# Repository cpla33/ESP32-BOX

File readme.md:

# ESP32-BOX

The device has been designed around regular ESP32-module to be fitted inside DIN-rail mounting enclosure. The board designed to be compact as much as possible. It takes 3 DIN-rail positions only.

------

### Main features:

- The **ESP32-BOX** has internal AC/DC-converter. Thus it could be powered from the regular AC line (i.e. wall socket) 100-240V (no external AC/DC adapters needed);
- The **ESP32-BOX** provides 4 optically isolated Relay outputs (up to 10A/250V or 5A/30V each). Each relay output has its own LED-indicator.
- The **ESP32-BOX** provides 4 GPIOs. Two of them could be used as I2C-line.
- All the inputs and outputs of the **ESP32-BOX** are implemented as reliable screw terminals.
- The **ESP32-BOX** has onboard RGB-led, which could be used for multiple status indications on your taste.
- The top part of the enclosure is transparent. So the LEDs could be easily observed from the outside.
- The **ESP32-BOX** provides powerful external antenna, which is located inside the enclosure. Thanks to `uFL/IPEX1` header any other suitable antenna could be used instead.
- The **ESP32-BOX** is equipped with the external +3dBi antenna hidden inside the enclosure;
- The **ESP32-BOX** could be programmed with the USB Type-C cable (no buttons required).
- The **ESP32-BOX** could be programmed with the ; write your sketches whenever you want: Arduino, CircuitPython, MicroPython or ESP-IDF.
- Finally, **ESP32-BOX** is **ESPHome**-compatible!

------

### Programming:

A number of different IDEs and programming languages of any taste as below are allowed to program the **ESP32-BOX**:

[ESPHome](https://www.binarytechlabs.com/how-to-flash-esphome-firmware-a-friendly-step-by-step-guide/)

[Arduino](https://randomnerdtutorials.com/installing-the-esp32-board-in-arduino-ide-windows-instructions/)

[CircuitPython](FIRMWARE/CIRCUITPYTHON/readme_circuitpython.md)

[MicroPython](https://micropython.org/download/ESP32_GENERIC/)

[ESP-IDF](https://docs.espressif.com/projects/esp-idf/en/stable/esp32/get-started/index.html)

A couple of different examples could be found in the [FIRMWARE](FIRMWARE/) folder.

------

### Pinout:

------

### Schematics:

Refer to the [schematics](HARDWARE/esp32_box_single.pdf) if needed.

------

Coming soon at Lectronz.com

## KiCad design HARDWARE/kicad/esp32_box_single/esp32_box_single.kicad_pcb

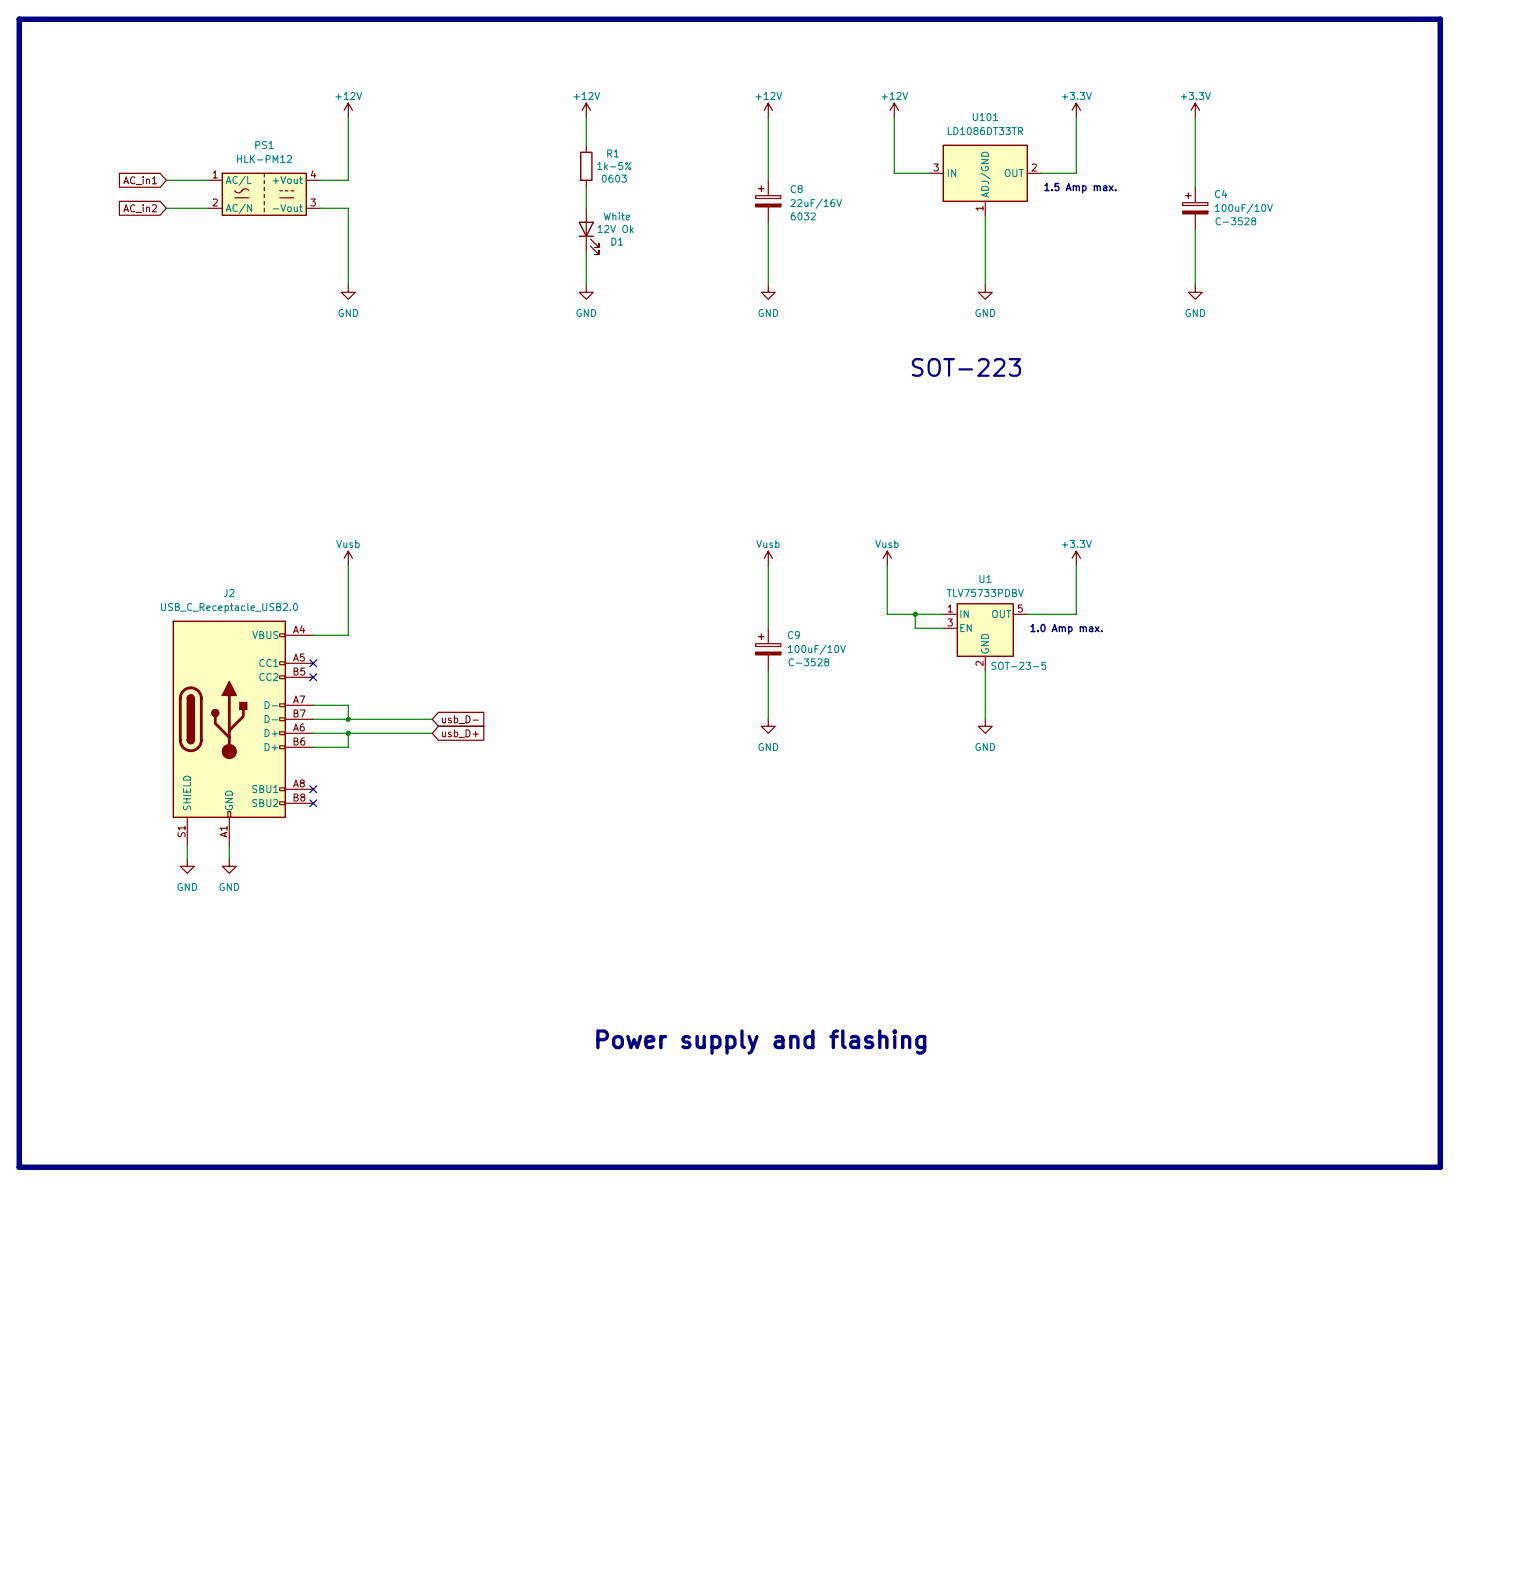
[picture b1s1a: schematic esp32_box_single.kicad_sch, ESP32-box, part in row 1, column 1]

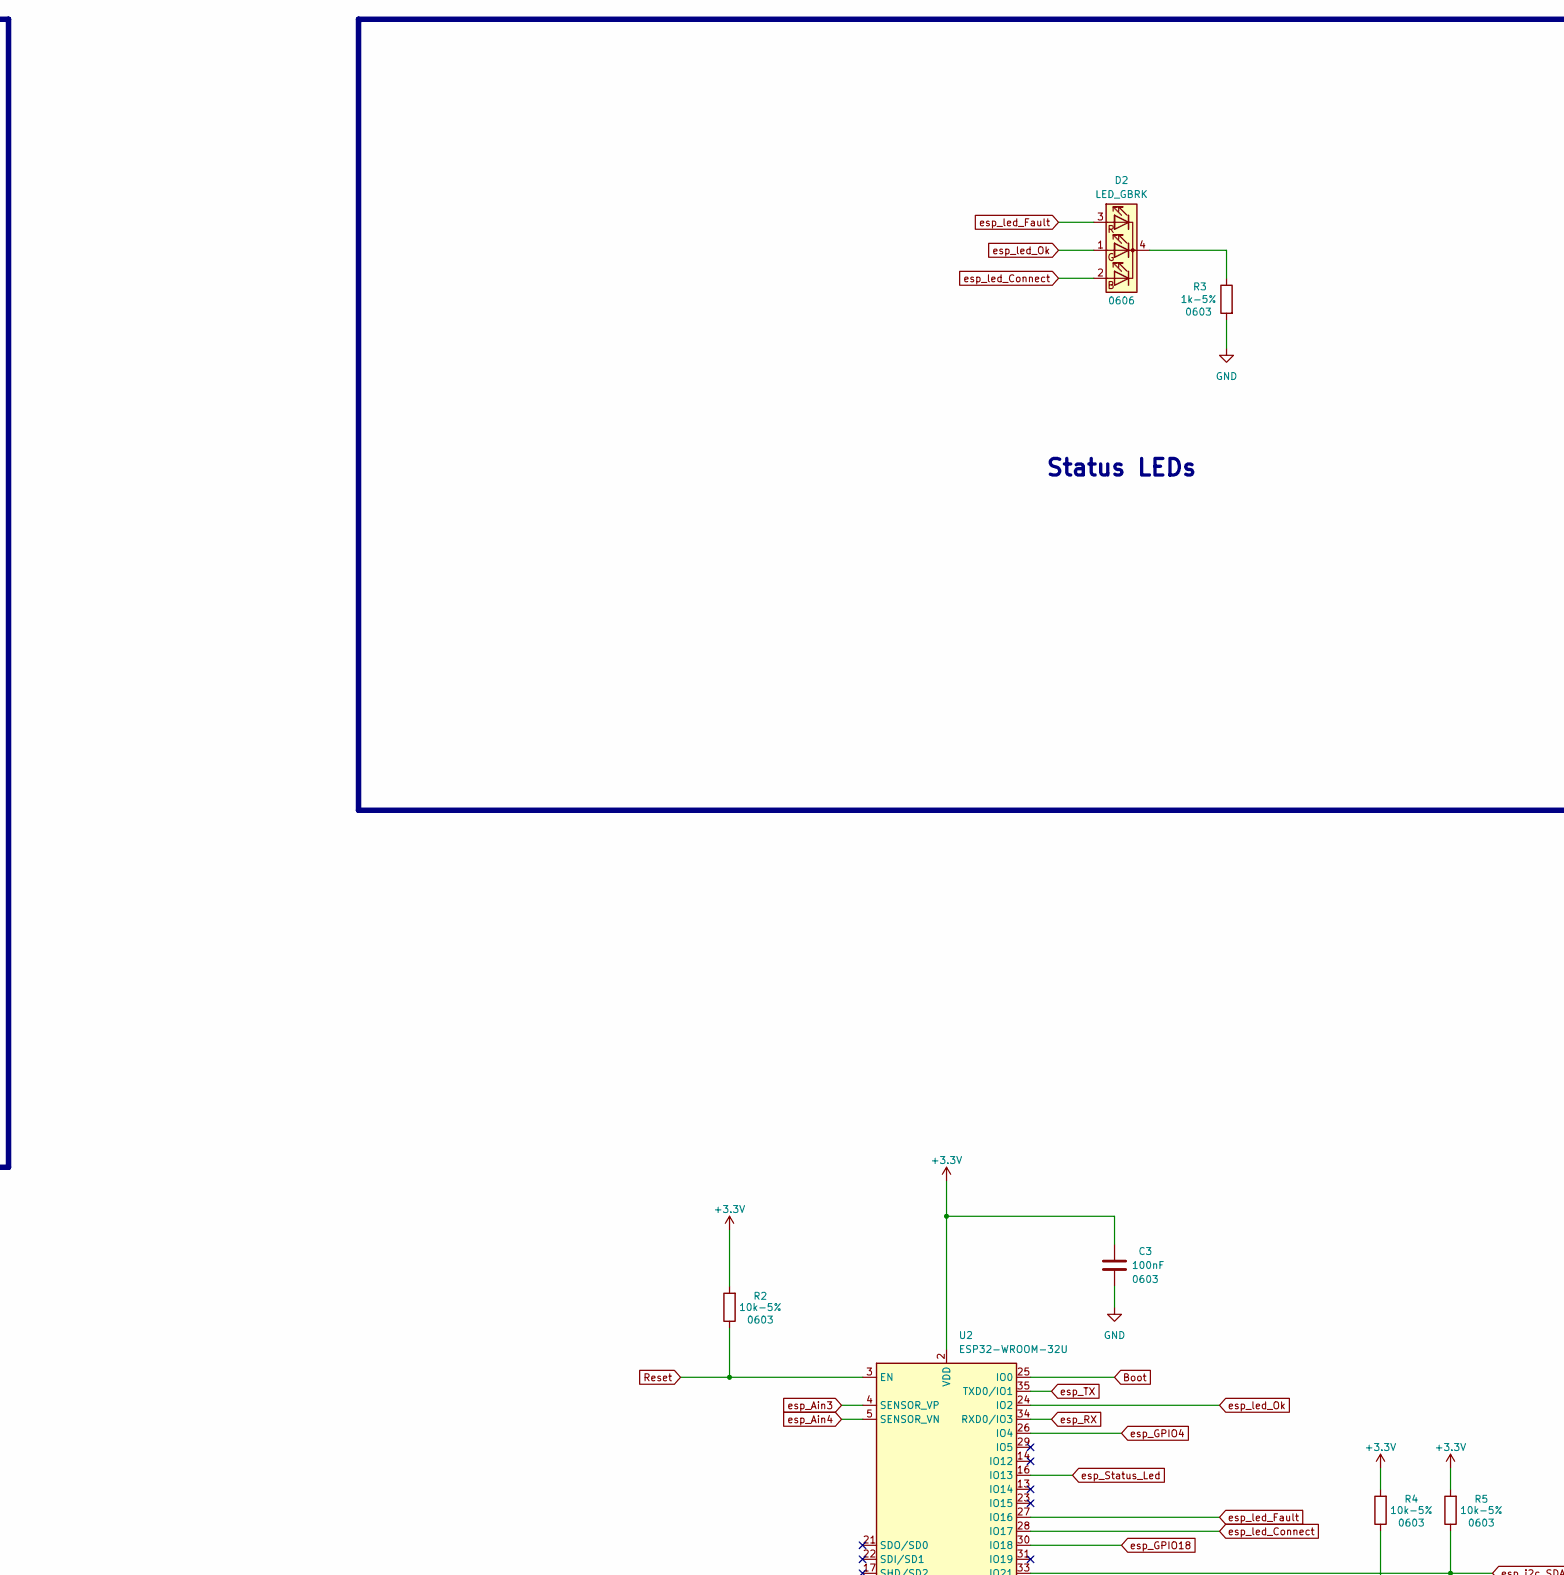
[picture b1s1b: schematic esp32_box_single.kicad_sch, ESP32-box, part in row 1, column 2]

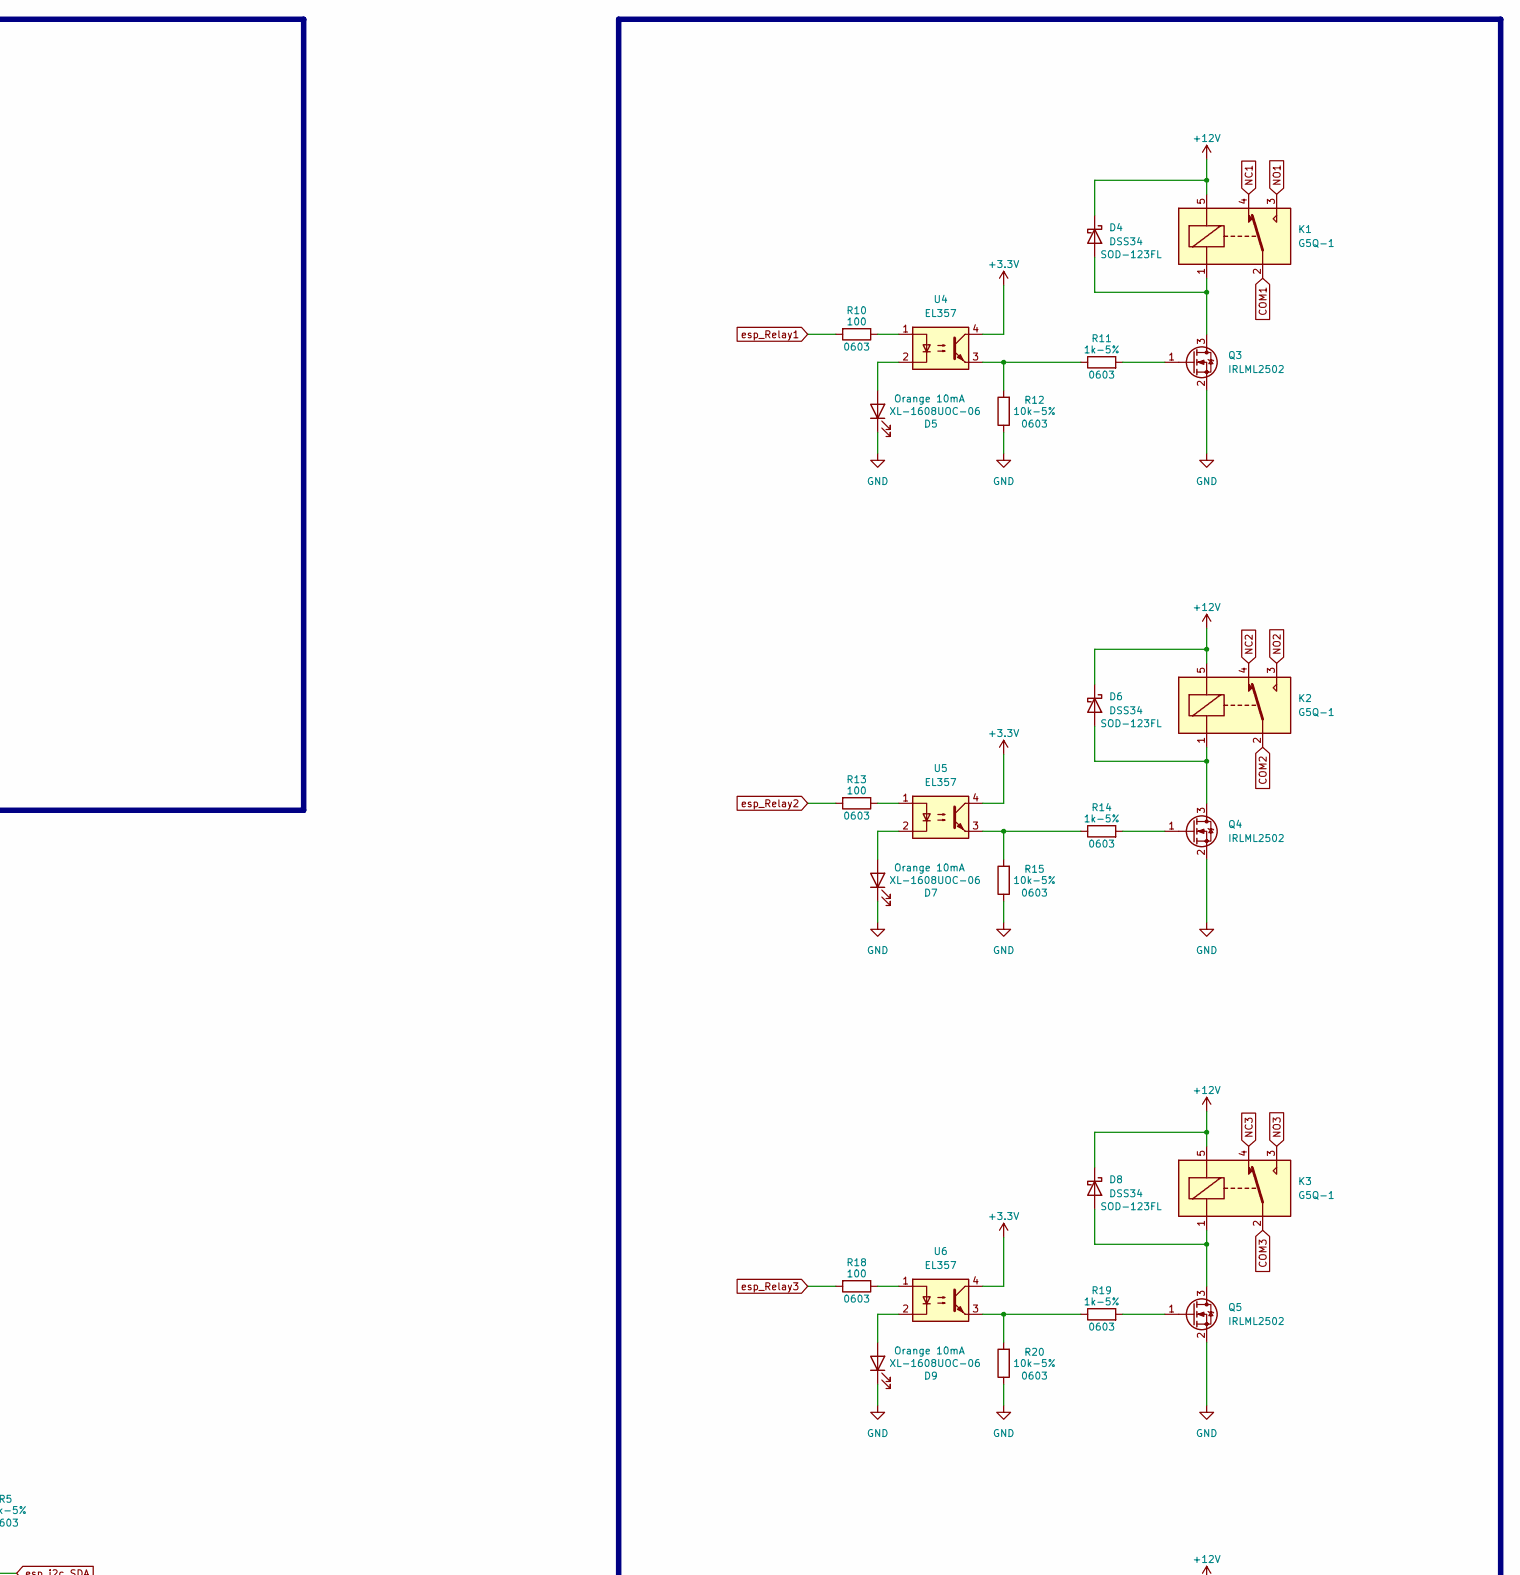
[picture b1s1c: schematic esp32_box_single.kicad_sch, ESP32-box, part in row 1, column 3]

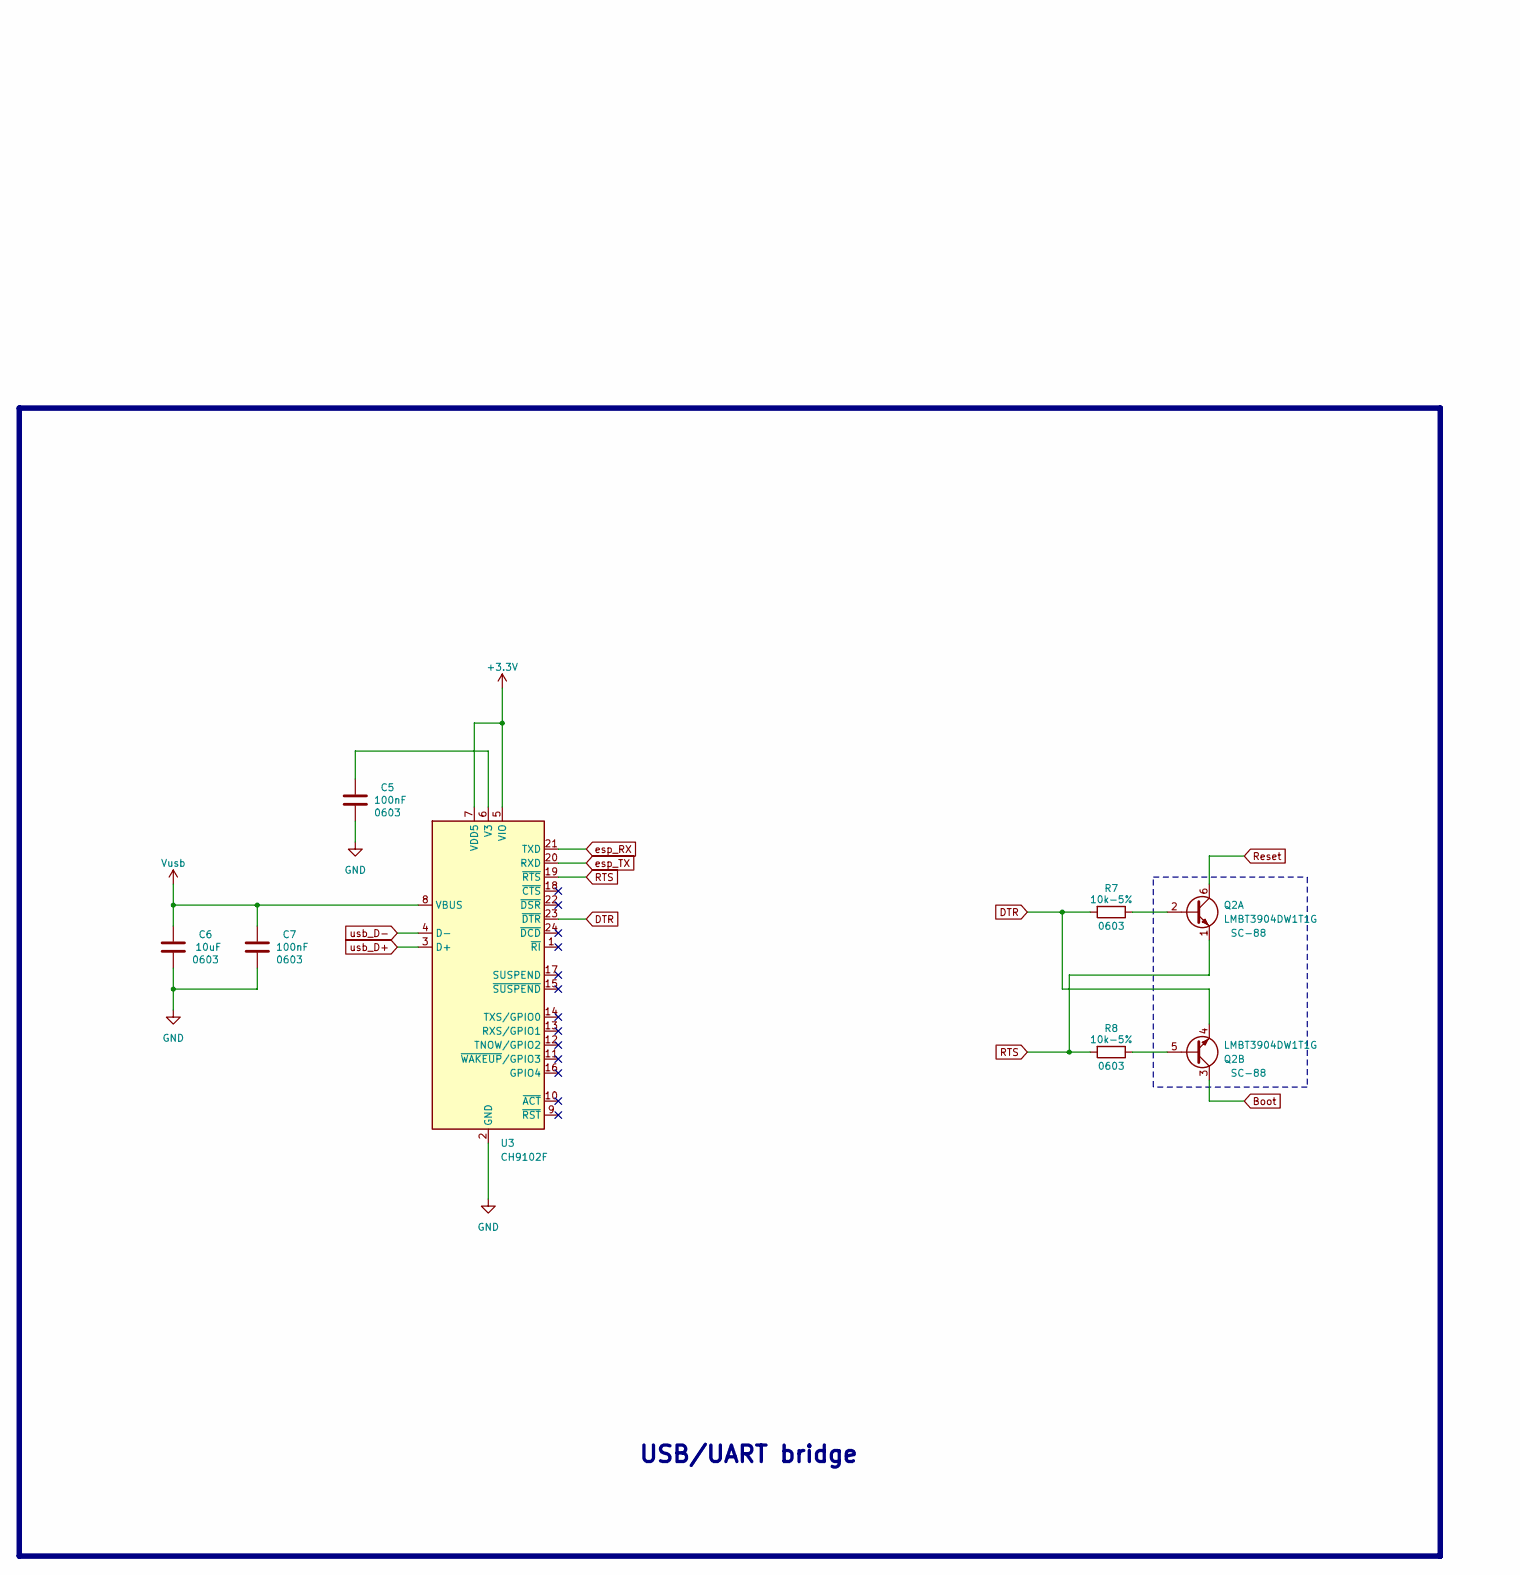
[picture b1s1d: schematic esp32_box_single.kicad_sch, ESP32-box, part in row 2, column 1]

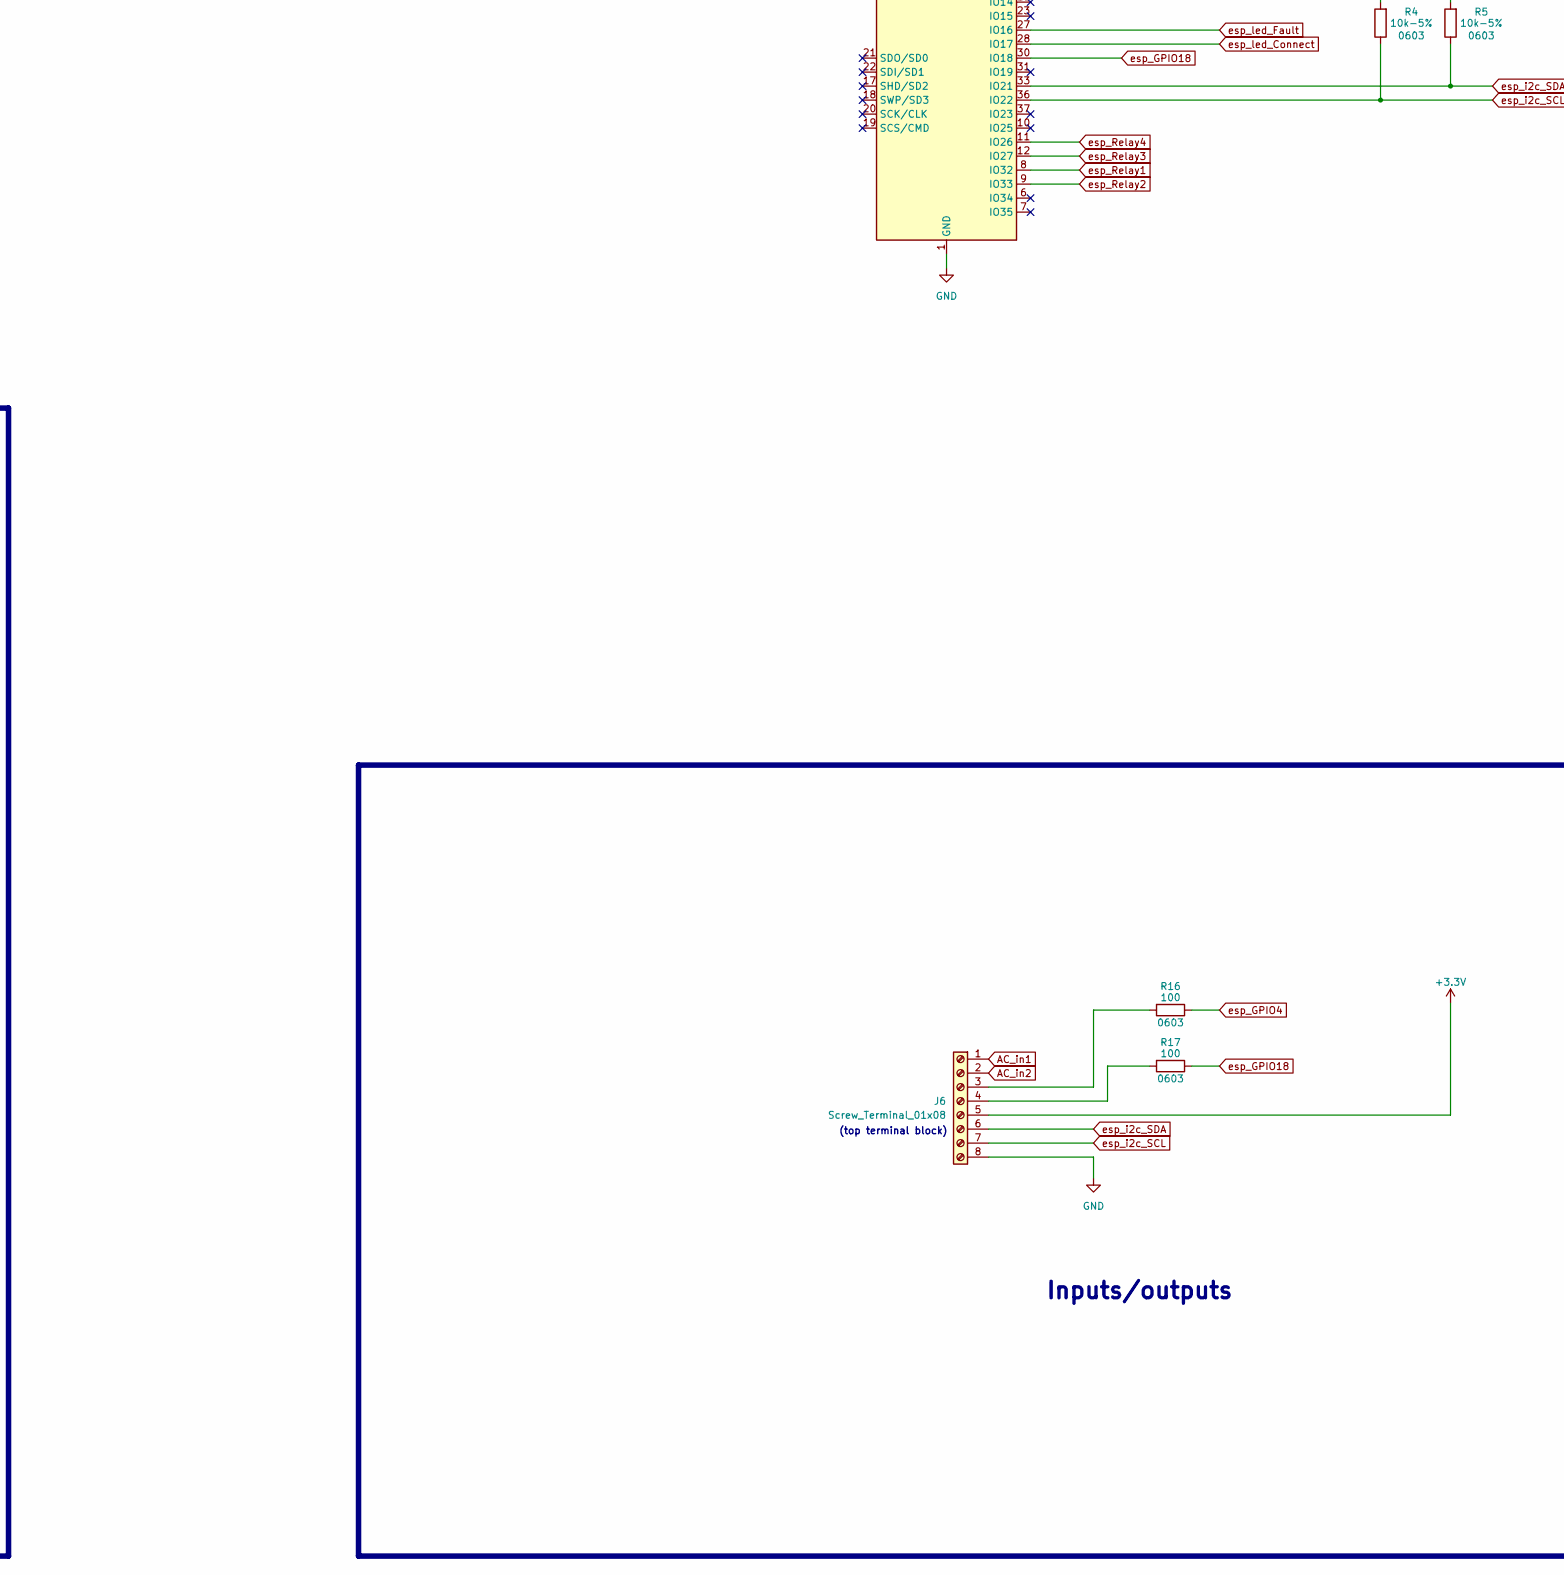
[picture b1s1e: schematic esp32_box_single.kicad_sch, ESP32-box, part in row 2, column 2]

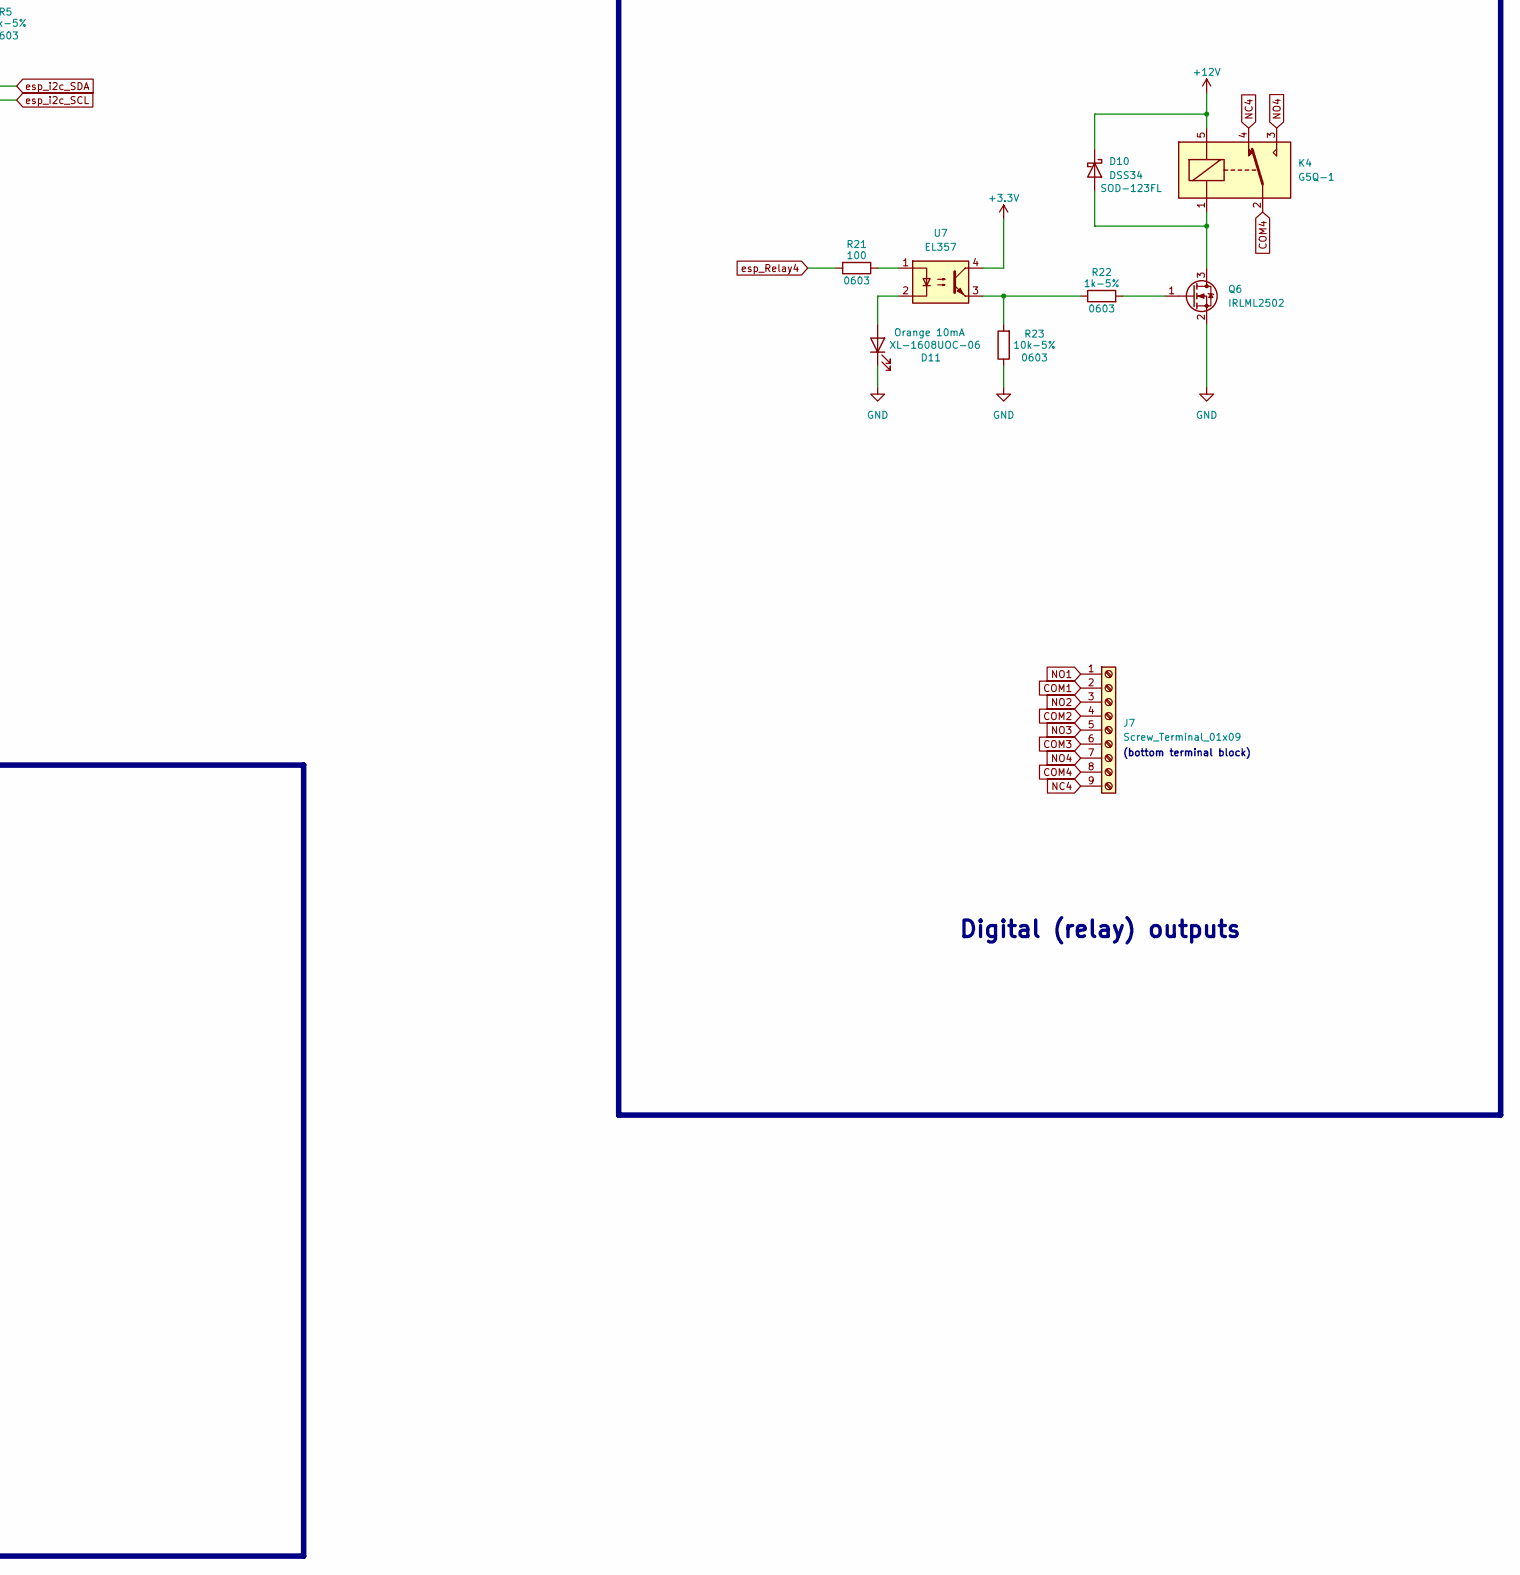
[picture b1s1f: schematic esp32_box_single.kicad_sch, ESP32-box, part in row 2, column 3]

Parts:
C3, C5, C7: 100nF; C_0603_1608Metric; LCSC part C1591
C4, C9: 100uF/10V; CP_EIA-3528-21_Kemet-B; LCSC part C122271
C6: 10uF; C_0603_1608Metric; LCSC part C19702
C8: 22uF/16V; CP_EIA-6032-20_AVX-F; LCSC part C11376
D1: 12V Ok; LED_0603_1608Metric; LCSC part C965808
D2: LED_GBRK; C273611_RGB_Led_0606; LCSC part C273611
D4, D6, D8, D10: DSS34; C2923958_DSS34_SOD-123FL; LCSC part C2923958
D5, D7, D9, D11: XL-1608UOC-06; LED_0603_1608Metric; LCSC part C434425
J2: USB_C_Receptacle_USB2.0; C3151749_USB_TYPE-C_Vertical; LCSC part C3151749
J6: Screw_Terminal_01x08; TerminalBlock_RND_205-00238_1x08_P5.08mm_Horizontal
J7: Screw_Terminal_01x09; TerminalBlock_RND_205-00239_1x09_P5.08mm_Horizontal
K1, K2, K3, K4: G5Q-1; C225715_Omron-G5Q
PS1: HLK-PM12; C209905_HLK-PM12_mod; LCSC part C209905
Q2: LMBT3904DW1T1G; SOT-363_SC-70-6; LCSC part C131781
Q3, Q4, Q5, Q6: IRLML2502; SOT-23; LCSC part C347503
R1, R3, R11, R14, R19, R22: 1k-5%; R_0603_1608Metric; LCSC part C2907113
R2, R4, R5, R7, R8, R12, R15, R20, R23: 10k-5%; R_0603_1608Metric; LCSC part C25804
R10, R13, R16, R17, R18, R21: 100; R_0603_1608Metric; LCSC part C2907089
U1: TLV75733PDBV; SOT-23-5; LCSC part C485517
U2: ESP32-WROOM-32U; LCSC part C328062
U3: CH9102F; QFN-24-1EP_4x4mm_P0.5mm_EP2.6x2.6mm; LCSC part C2858418
U4, U5, U6, U7: EL357; C42381015_EL357_L4.4-W4.1-P2.54-LS7.0-TL; LCSC part C42381015
U101: LD1086DT33TR; TO-252-2; LCSC part C12051

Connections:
+3.3V: C3.2, C4.1, J6.5, R2.2, R4.2, R5.2, U1.5 (OUT), U2.2 (VDD), U3.5 (VIO), U3.7 (VDD5), U4.4, U5.4, U6.4, U7.4, U101.2 (OUT)
+12V: C8.1, D4.1 (K), D6.1 (K), D8.1 (K), D10.1 (K), K1.5, K2.5, K3.5, K4.5, PS1.4 (+Vout), R1.1, U101.3 (IN)
AC_in1: J6.1, PS1.1 (AC/L)
AC_in2: J6.2, PS1.2 (AC/N)
Boot: Q2.3 (C2), U2.25 (IO0)
COM1: J7.2, K1.2
COM2: J7.4, K2.2
COM3: J7.6, K3.2
COM4: J7.8, K4.2
DTR: Q2.4 (E2), R7.2, U3.23 (~DTR)
GND: C3.1, C4.2, C5.1, C6.1, C7.1, C8.2, C9.2, D1.1 (K), D5.1 (K), D7.1 (K), D9.1 (K), D11.1 (K), J2.A1 (GND), J2.A12 (GND), J2.B1 (GND), J2.B12 (GND), J2.S1 (SHIELD), J6.8, PS1.3 (-Vout), Q3.2 (S), Q4.2 (S), Q5.2 (S), Q6.2 (S), R3.2, R12.1, R15.1, R20.1, R23.1, U1.2 (GND), U2.1 (GND), U2.15 (GND), U2.38 (GND), U2.39 (GND), U3.2 (GND), U3.25 (GND), U101.1 (ADJ/GND); also elsewhere on the board
NC1: K1.4
NC2: K2.4
NC3: K3.4
NC4: J7.9, K4.4
NO1: J7.1, K1.3
NO2: J7.3, K2.3
NO3: J7.5, K3.3
NO4: J7.7, K4.3
unnamed: D1.2 (A), R1.2
unnamed: D2.4 (K), R3.1
unnamed: D4.2 (A), K1.1, Q3.3 (D)
unnamed: D5.2 (A), U4.2
unnamed: D6.2 (A), K2.1, Q4.3 (D)
unnamed: D7.2 (A), U5.2
unnamed: D8.2 (A), K3.1, Q5.3 (D)
unnamed: D9.2 (A), U6.2
unnamed: D10.2 (A), K4.1, Q6.3 (D)
unnamed: D11.2 (A), U7.2
unnamed: J6.3, R16.2
unnamed: J6.4, R17.2
unnamed: Q2.2 (B1), R7.1
unnamed: Q2.5 (B2), R8.1
unnamed: Q3.1 (G), R11.2
unnamed: Q4.1 (G), R14.2
unnamed: Q5.1 (G), R19.2
unnamed: Q6.1 (G), R22.2
unnamed: R10.1, U4.1
unnamed: R11.1, R12.2, U4.3
unnamed: R13.1, U5.1
unnamed: R14.1, R15.2, U5.3
unnamed: R18.1, U6.1
unnamed: R19.1, R20.2, U6.3
unnamed: R21.1, U7.1
unnamed: R22.1, R23.2, U7.3
unnamed: C5.2, U3.6 (V3)
unnamed 46: U3.9 (~RST); also elsewhere on the board
RTS: Q2.1 (E1), R8.2, U3.19 (~RTS)
Reset: Q2.6 (C1), R2.1, U2.3 (EN)
Vusb: C6.2, C7.2, C9.1, J2.A4 (VBUS), J2.A9 (VBUS), J2.B4 (VBUS), J2.B9 (VBUS), U1.1 (IN), U1.3 (EN), U3.8 (VBUS)
esp_Ain1: U2.6 (IO34)
esp_Ain2: U2.7 (IO35)
esp_Ain3: U2.4 (SENSOR_VP)
esp_Ain4: U2.5 (SENSOR_VN)
esp_GPIO4: R16.1, U2.26 (IO4)
esp_GPIO18: R17.1, U2.30 (IO18)
esp_GPIO19: U2.31 (IO19)
esp_GPIO23: U2.37 (IO23)
esp_RX: U2.34 (RXD0/IO3), U3.21 (TXD)
esp_Relay1: R10.2, U2.8 (IO32)
esp_Relay2: R13.2, U2.9 (IO33)
esp_Relay3: R18.2, U2.12 (IO27)
esp_Relay4: R21.2, U2.11 (IO26)
esp_Status_Led: U2.16 (IO13)
esp_TX: U2.35 (TXD0/IO1), U3.20 (RXD)
esp_i2c_SCL: J6.7, R4.1, U2.36 (IO22)
esp_i2c_SDA: J6.6, R5.1, U2.33 (IO21)
esp_led_Connect: D2.2 (BA), U2.28 (IO17)
esp_led_Fault: D2.3 (RA), U2.27 (IO16)
esp_led_Ok: D2.1 (GA), U2.24 (IO2)
usb_D+: J2.A6 (D+), J2.B6 (D+), U3.3 (D+)
usb_D-: J2.A7 (D-), J2.B7 (D-), U3.4 (D-)

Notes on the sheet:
Digital (relay) outputs
USB/UART bridge
Power supply and flashing
(bottom terminal block)
Status LEDs
Inputs/outputs
SOT-223
1.5 Amp max.
(top terminal block)
1.0 Amp max.

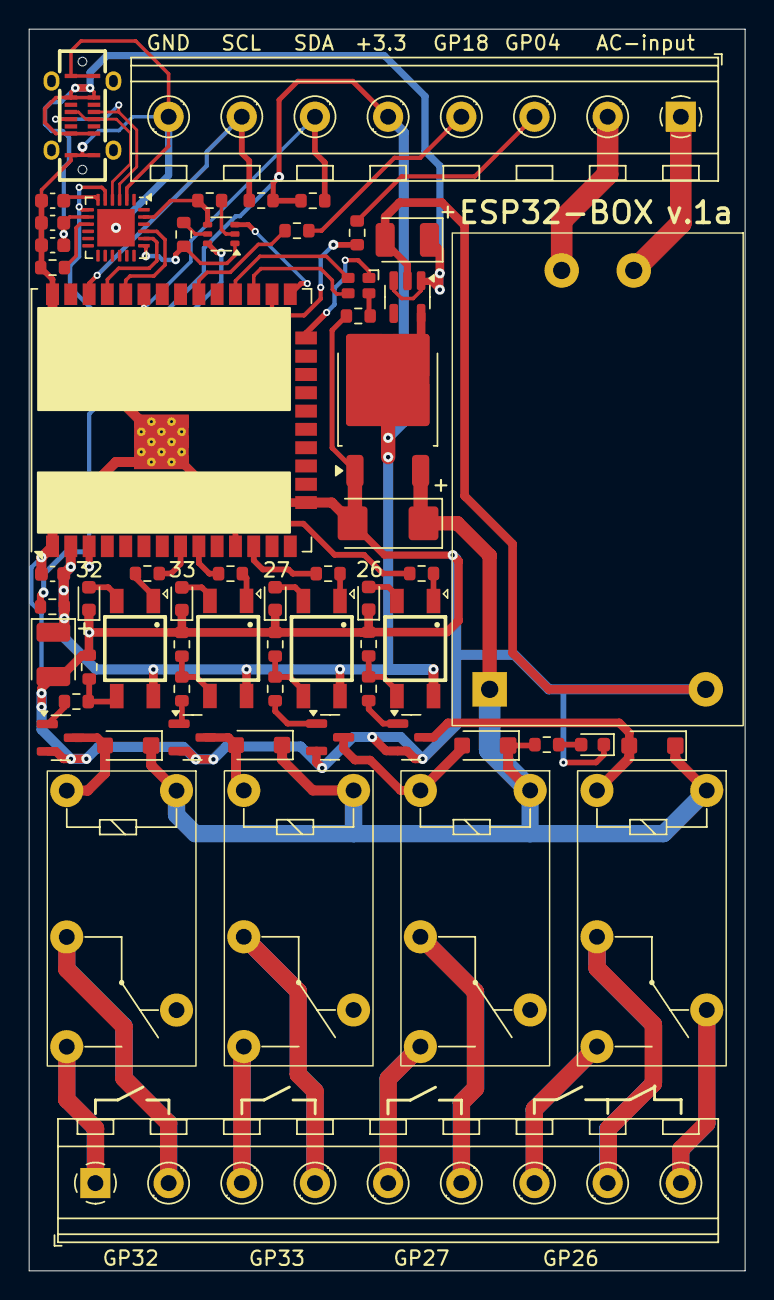
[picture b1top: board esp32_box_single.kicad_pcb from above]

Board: 2 copper layers, 49.7 x 86.2 mm, 60 parts (0 on the bottom side), 62 nets.

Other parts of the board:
R9: 10k-5%; R_0603_1608Metric

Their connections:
GND: R9.1; also elsewhere on the board
unnamed 46: R9.2; also elsewhere on the board

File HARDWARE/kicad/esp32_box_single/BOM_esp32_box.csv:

"Reference","Value","Manufacturer","LCSC part"
"C3","100nF","Samsung Electro-Mechanics","C1591"
"C4","100uF/10V","Kemet","C122271"
"C5","100nF","Samsung Electro-Mechanics","C1591"
"C6","10uF","Samsung Electro-Mechanics","C19702"
"C7","100nF","Samsung Electro-Mechanics","C1591"
"C8","22uF/16V","Kyocera AVX","C11376"
"C9","100uF/10V","Kemet","C122271"
"D1","12V Ok","XINGLIGHT","C965808"
"D2","LED_GBRK","TOGIALED","C273611"
"D4","DSS34","Jiangsu Changjing Electronics Technology Co., Ltd.","C2923958"
"D5","XL-1608UOC-06","Yongyu Photoelectric","C434425"
"D6","DSS34","Jiangsu Changjing Electronics Technology Co., Ltd.","C2923958"
"D7","XL-1608UOC-06","Yongyu Photoelectric","C434425"
"D8","DSS34","Jiangsu Changjing Electronics Technology Co., Ltd.","C2923958"
"D9","XL-1608UOC-06","Yongyu Photoelectric","C434425"
"D10","DSS34","Jiangsu Changjing Electronics Technology Co., Ltd.","C2923958"
"D11","XL-1608UOC-06","Yongyu Photoelectric","C434425"
"J2","USB_C_Receptacle_USB2.0","SHOU HAN","C3151749"
"Q2","LMBT3904DW1T1G","LRC","C131781"
"Q3","IRLML2502","UMW","C347503"
"Q4","IRLML2502","UMW","C347503"
"Q5","IRLML2502","UMW","C347503"
"Q6","IRLML2502","UMW","C347503"
"R1","1k-5%","FOJAN","C2907113"
"R2","10k-5%","UNI-ROYAL(Uniroyal Elec)","C25804"
"R3","1k-5%","FOJAN","C2907113"
"R4","10k-5%","UNI-ROYAL(Uniroyal Elec)","C25804"
"R5","10k-5%","UNI-ROYAL(Uniroyal Elec)","C25804"
"R7","10k-5%","UNI-ROYAL(Uniroyal Elec)","C25804"
"R8","10k-5%","UNI-ROYAL(Uniroyal Elec)","C25804"
"R9","10k-5%","UNI-ROYAL(Uniroyal Elec)","C25804"
"R10","100","FOJAN","C2907089"
"R11","1k-5%","FOJAN","C2907113"
"R12","10k-5%","UNI-ROYAL(Uniroyal Elec)","C25804"
"R13","100","FOJAN","C2907089"
"R14","1k-5%","FOJAN","C2907113"
"R15","10k-5%","UNI-ROYAL(Uniroyal Elec)","C25804"
"R16","100","FOJAN","C2907089"
"R17","100","FOJAN","C2907089"
"R18","100","FOJAN","C2907089"
"R19","1k-5%","FOJAN","C2907113"
"R20","10k-5%","UNI-ROYAL(Uniroyal Elec)","C25804"
"R21","100","FOJAN","C2907089"
"R22","1k-5%","FOJAN","C2907113"
"R23","10k-5%","UNI-ROYAL(Uniroyal Elec)","C25804"
"U1","TLV75733PDBV","Texas Instruments","C485517"
"U2","ESP32-WROOM-32U","Espressif","C328062"
"U3","CH9102F","WCH(Jiangsu Qin Heng)","C2858418"
"U4","EL357","Everlight Elec","C42381015"
"U5","EL357","Everlight Elec","C42381015"
"U6","EL357","Everlight Elec","C42381015"
"U7","EL357","Everlight Elec","C42381015"
"U101","LD1086DT33TR","STMicroelectronics","C12051"

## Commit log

2025-06-22 pre-test1
2025-07-07 update 2025-07-07
2025-07-07 gitignore updated
2025-07-07 upd3
2025-07-07 upd4
2025-07-07 upd5
2025-07-21 readme.md modified
    Features picture added
2025-07-21 CircuitPython support has been added
    CircuitPython readme and example has been added
2025-07-21 Schematics link has been added
2025-07-21 readme_circuitpython update
